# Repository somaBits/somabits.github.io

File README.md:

[How to build a Soma Vibe Bit](https://github.com/somaBits/somabits.github.io/wiki/How-to-Build-a-Soma-Vibe-Bit)

[How to build a Soma Heat Bit](https://github.com/somaBits/somabits.github.io/wiki/How-to-Build-a-Soma-Heat-Bit)

[Coming soon - How to build a Soma Inflatable Bit](../../wiki/)

## Background

The Soma Bits are a very basic set of actuators (read: something that can vibrate, heat up or expand/contract) based on the arduino platform. With them you can explore how vibration, heat and inflatables feel without having to focus on the technical stuff. They have a very simple interface on purpose and also simple approach on how to build them. They are designed to be usable after they are built and for newcomers to explore how they work on three levels:
1. How interactive technology (in this case vibration, heat and inflatables) feels and use it without having to know how it works (intially).
2. How the Soma Bits and therefore interactive technology works by looking at its commpenents.
3. Build a Soma Bit yourself to understand the technical side of it.

We wrote a research paper about it. If you'd like to have a bit more background and reasoning about it, have a look: [http://dl.acm.org/citation.cfm?id=3533510](http://dl.acm.org/citation.cfm?id=3533510)

<!--
**somaBits/somabits** is a ✨ _special_ ✨ repository because its `README.md` (this file) appears on your GitHub profile.

Here are some ideas to get you started:

- 🔭 I’m currently working on ...
- 🌱 I’m currently learning ...
- 👯 I’m looking to collaborate on ...
- 🤔 I’m looking for help with ...
- 💬 Ask me about ...
- 📫 How to reach me: ...
- 😄 Pronouns: ...
- ⚡ Fun fact: ...
-->

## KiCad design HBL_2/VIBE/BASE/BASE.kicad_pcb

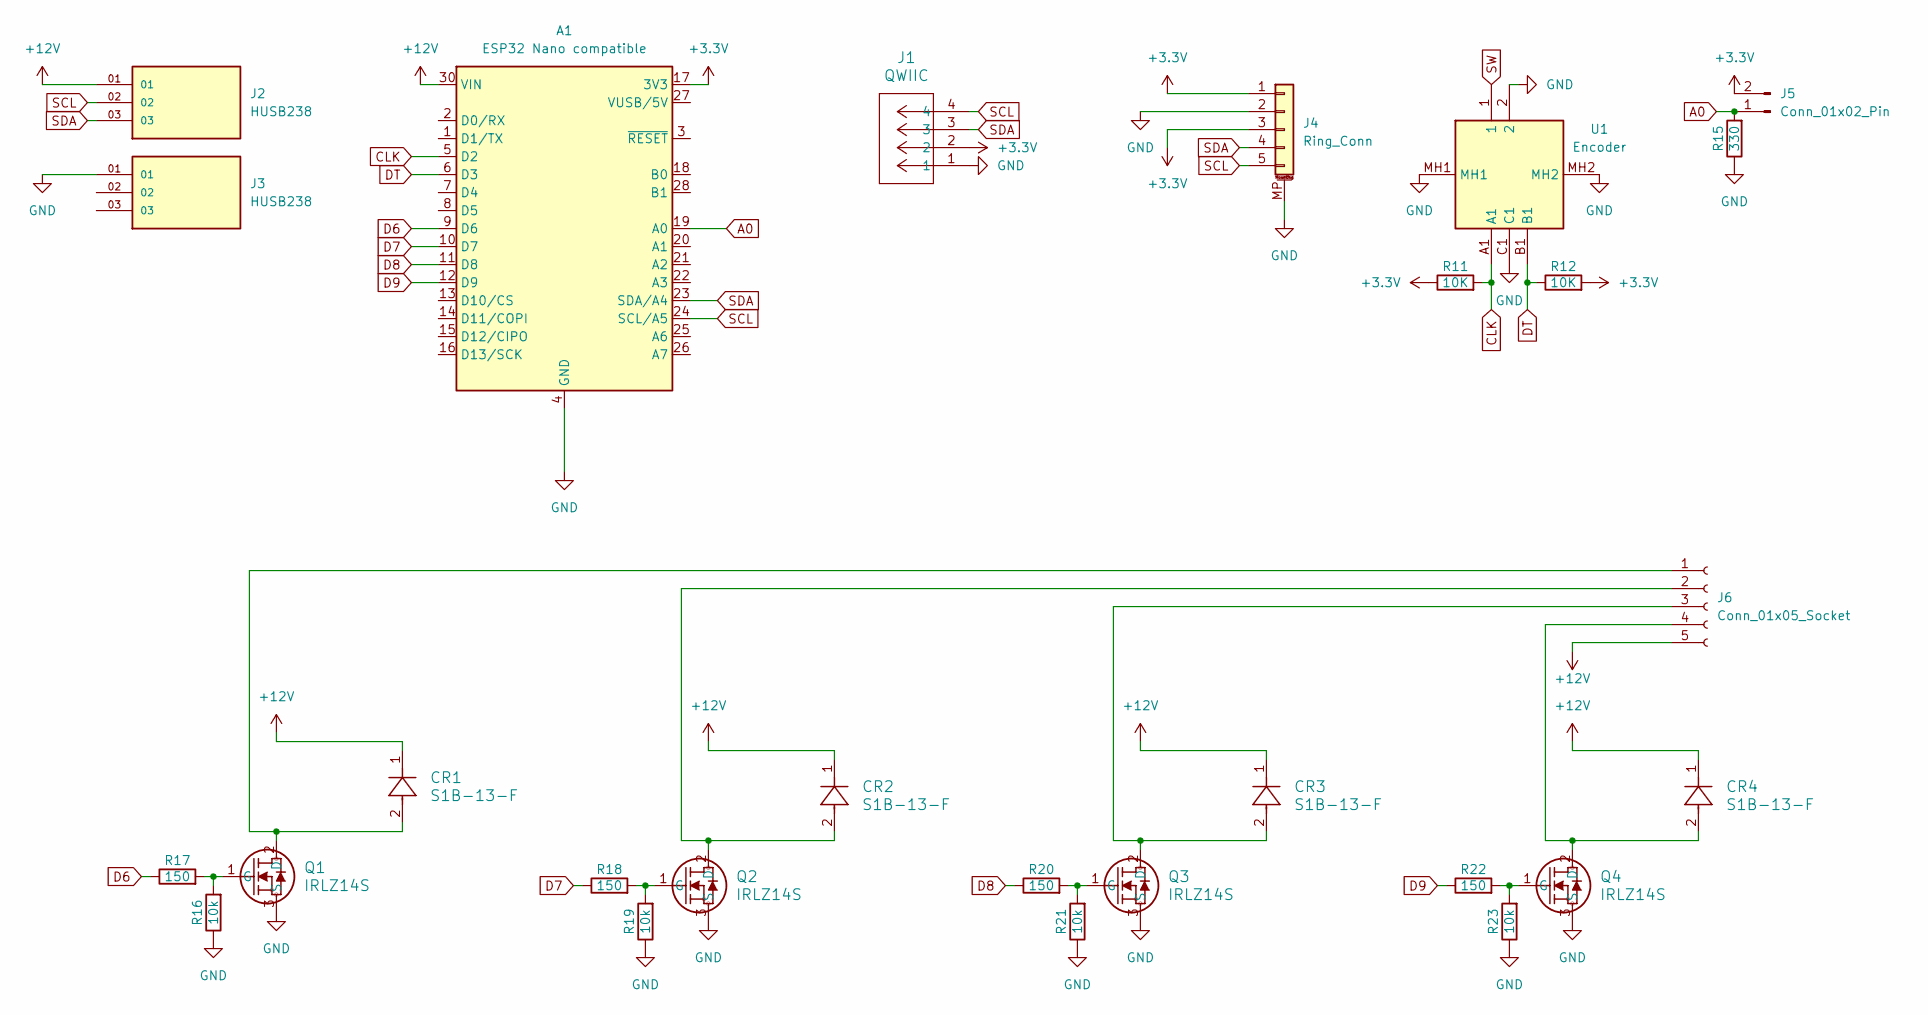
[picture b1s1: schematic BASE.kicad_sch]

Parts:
A1: ESP32 Nano compatible; Arduino_Nano
CR1, CR2, CR3, CR4: S1B-13-F; D_DO-35_SOD27_P7.62mm_Horizontal
J1: QWIIC; CONN_SM04B-SRSS-TB_JST
J2, J3: HUSB238; SAMTEC_SL-103-G-39; PARTREV R
J4: Ring_Conn; Molex_PicoBlade_53261-0571_1x05-1MP_P1.25mm_Horizontal
J5: Conn_01x02_Pin; PinSocket_1x02_P2.54mm_Vertical
J6: Conn_01x05_Socket; PinHeader_1x05_P2.54mm_Horizontal
Q1, Q2, Q3, Q4: IRLZ14S; TO254P465X1031X1954-3P
R11, R12: 10K; R_Axial_DIN0204_L3.6mm_D1.6mm_P7.62mm_Horizontal
R15: 330; R_Axial_DIN0204_L3.6mm_D1.6mm_P7.62mm_Horizontal
R16, R19, R21, R23: 10k; R_Axial_DIN0204_L3.6mm_D1.6mm_P7.62mm_Horizontal
R17, R18, R20, R22: 150; R_Axial_DIN0204_L3.6mm_D1.6mm_P7.62mm_Horizontal
U1: Encoder; PEC11L4120FS0020; Manufacturer_Part_Number PEC11L-4020F-S0020; Mouser Part Number 652-PEC11L4020FS0020

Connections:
+3.3V: A1.17 (3V3), J1.2, J4.1 (VCC), J4.3 (VIO), J5.2, R11.1, R12.2
+12V: A1.30 (VIN), CR1.1, CR2.1, CR3.1, CR4.1, J2.01, J6.5
A0: A1.19 (A0), J5.1, R15.2
CLK: A1.5 (D2), R11.2, U1.A1
D6: A1.9 (D6), R17.1
D7: A1.10 (D7), R18.1
D8: A1.11 (D8), R20.1
D9: A1.12 (D9), R22.1
DT: A1.6 (D3), R12.1, U1.B1
GND: A1.4 (GND), A1.29 (GND), J1.1, J3.01, J4.2 (GND), J4.MP (MountPin), Q1.3 (S), Q2.3 (S), Q3.3 (S), Q4.3 (S), R15.1, R16.1, R19.1, R21.1, R23.1, U1.2, U1.C1, U1.MH1, U1.MH2
unnamed: CR1.2, J6.1, Q1.2 (D)
unnamed: CR2.2, J6.2, Q2.2 (D)
unnamed: CR3.2, J6.3, Q3.2 (D)
unnamed: CR4.2, J6.4, Q4.2 (D)
unnamed: Q1.1 (G), R16.2, R17.2
unnamed: Q2.1 (G), R18.2, R19.2
unnamed: Q3.1 (G), R20.2, R21.2
unnamed: Q4.1 (G), R22.2, R23.2
SCL: A1.24 (SCL/A5), J1.4, J2.02, J4.5 (SCL)
SDA: A1.23 (SDA/A4), J1.3, J2.03, J4.4 (SDA)
SW: U1.1

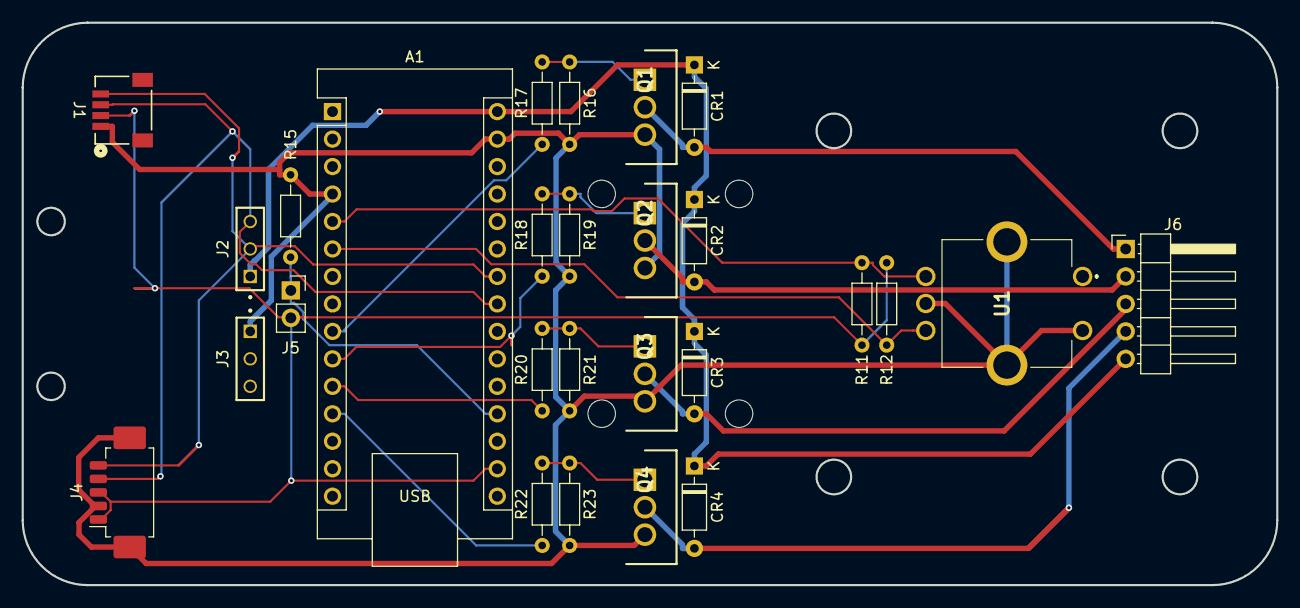
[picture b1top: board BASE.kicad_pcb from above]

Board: 2 copper layers, 116.0 x 52.0 mm, 27 parts (0 on the bottom side), 20 nets.

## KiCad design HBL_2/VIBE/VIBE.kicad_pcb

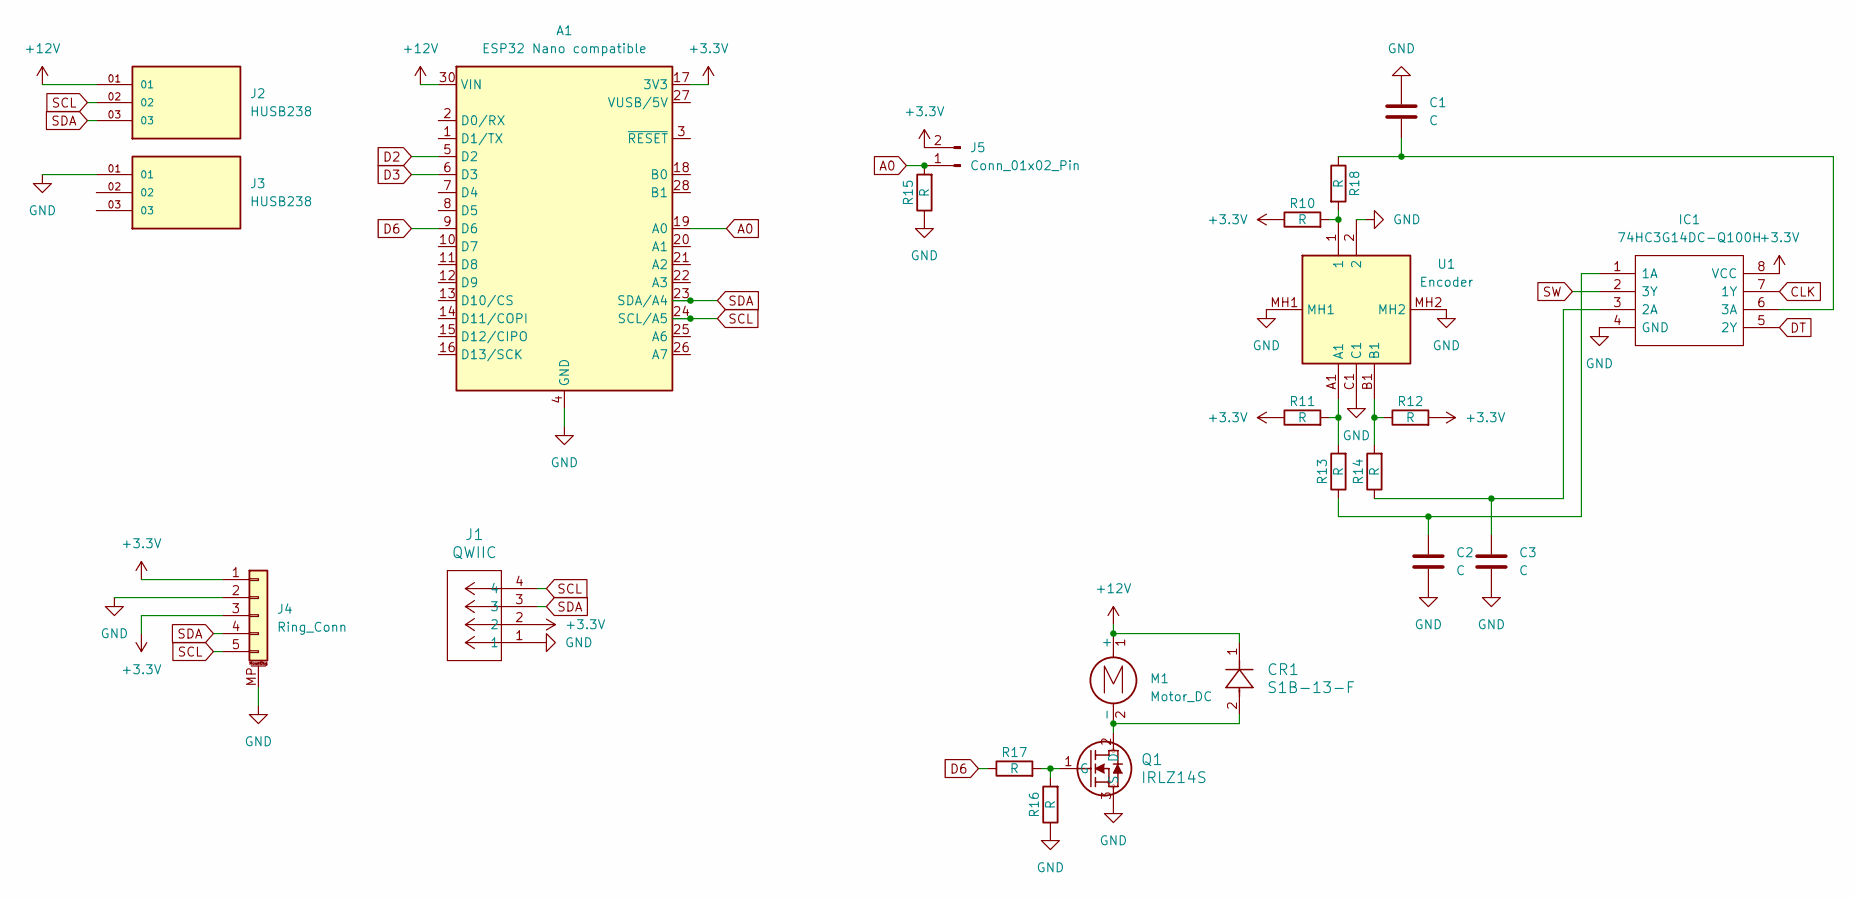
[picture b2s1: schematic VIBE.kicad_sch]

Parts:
A1: ESP32 Nano compatible; Arduino_Nano
C1, C2, C3: C; C_0201_0603Metric
CR1: S1B-13-F; SMA_DIO
IC1: 74HC3G14DC-Q100H; SOP50P310X100-8N; Manufacturer_Part_Number 74HC3G14DC-Q100H; Mouser Part Number 771-74HC3G14DCQ100H
J1: QWIIC; CONN_SM04B-SRSS-TB_JST
J2, J3: HUSB238; SAMTEC_SL-103-G-39; PARTREV R
J4: Ring_Conn; Molex_PicoBlade_53261-0571_1x05-1MP_P1.25mm_Horizontal
J5: Conn_01x02_Pin; PinSocket_1x02_P2.54mm_Vertical
M1: Motor_DC; PinHeader_1x02_P2.54mm_Horizontal
Q1: IRLZ14S; TO_Z14S_VIS
R10, R11, R12, R13, R14, R15, R16, R17, R18: R; RESC2012X60N
U1: Encoder; PEC11L4120FS0020; Manufacturer_Part_Number PEC11L-4020F-S0020; Mouser Part Number 652-PEC11L4020FS0020

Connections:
+3.3V: A1.17 (3V3), IC1.8 (VCC), J1.2, J4.1 (VCC), J4.3 (VIO), J5.2, R10.1, R11.1, R12.2
+12V: A1.30 (VIN), CR1.1, J2.01, M1.1 (+)
A0: A1.19 (A0), J5.1, R15.2; also elsewhere on the board
CLK: IC1.7 (1Y)
D2: A1.5 (D2)
D3: A1.6 (D3)
D6: A1.9 (D6), R17.1
DT: IC1.5 (2Y)
GND: A1.4 (GND), A1.29 (GND), C1.1, C2.2, C3.2, IC1.4 (GND), J1.1, J3.01, J4.2 (GND), J4.MP (MountPin), Q1.3 (S), R15.1, R16.1, U1.2, U1.C1, U1.MH1, U1.MH2; also elsewhere on the board
unnamed: C2.1, IC1.1 (1A), R13.1
unnamed: C3.1, IC1.3 (2A), R14.1
unnamed: C1.2, IC1.6 (3A), R18.1
unnamed: CR1.2, M1.2 (-), Q1.2 (D)
unnamed: Q1.1 (G), R16.2, R17.2
unnamed: R10.2, R18.2, U1.1
unnamed: R11.2, R13.2, U1.A1
unnamed: R12.1, R14.2, U1.B1
SCL: A1.24 (SCL/A5), J1.4, J2.02, J4.5 (SCL)
SDA: A1.23 (SDA/A4), J1.3, J2.03, J4.4 (SDA)
SW: IC1.2 (3Y)

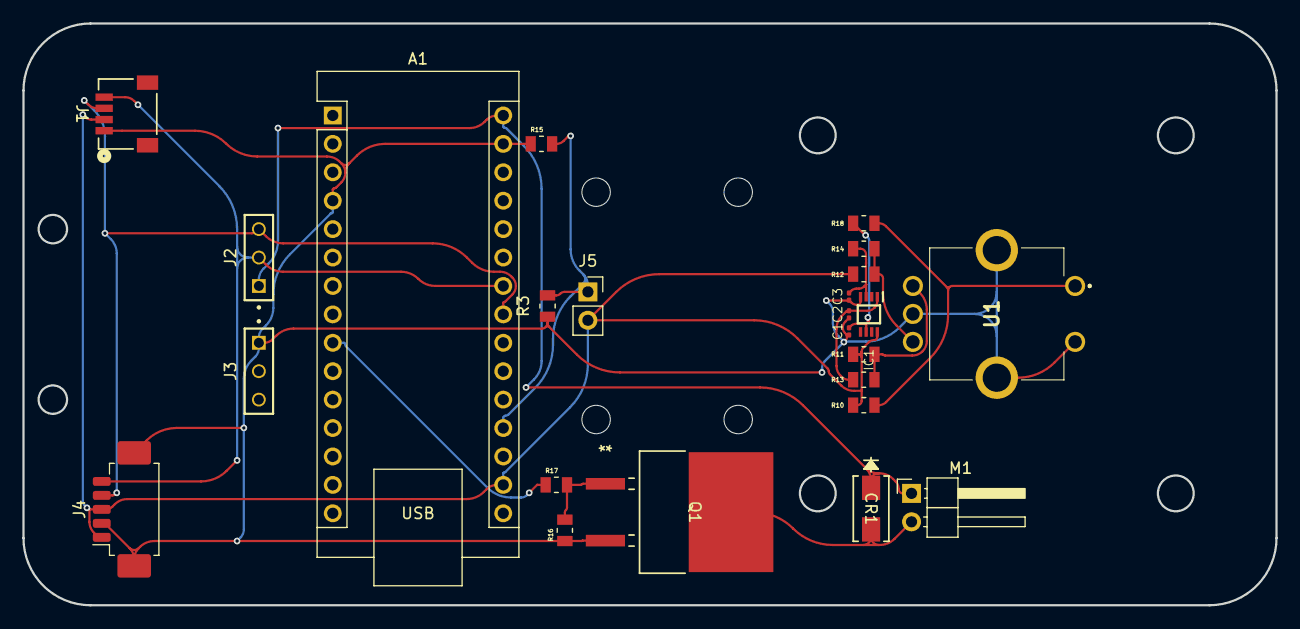
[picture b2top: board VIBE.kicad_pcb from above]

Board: 2 copper layers, 112.0 x 52.0 mm, 24 parts (0 on the bottom side), 15 nets.

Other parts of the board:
R3: RC0805FR-0710KL; RESC2012X60N

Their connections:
A0: R3.2; also elsewhere on the board
GND: R3.1; also elsewhere on the board

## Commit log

2022-04-20 Set theme jekyll-theme-minimal
2022-05-16 Set theme jekyll-theme-slate
2022-06-16 folder structure
2022-06-16 Schematics
2022-06-17 Added arduino code
2023-02-13 Fixed wrong link
2025-05-05 v0.1
    The first attempt in KiCAD. A mix between vibro actuator and heat.
    Next step is to incorporate the rest for the inflatable bit.
2025-05-05 Delete HBL_2/VIBE directory
    starting over
2025-05-06 changed encoder and trhoughhole parts
2025-05-23 notes
